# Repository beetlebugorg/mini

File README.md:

# Mini

<picture>
  <source media="(prefers-color-scheme: dark)" srcset="docs/lineart/img/hero-dark.png">
  
</picture>

A Bluetooth desk speaker that you print in three colors of PLA. Two Dayton Audio PC68-4
drivers and a ZK-502C Bluetooth amplifier sit in a sealed box of 166 × 108 × 94 mm. The
grille and the control strip snap on over four flush socket head screws.

- Website: https://beetlebug.org/mini/
- Spec sheet and build steps: [docs/Bluespeaker-Mini-Specs.pdf](docs/Bluespeaker-Mini-Specs.pdf)
- Drawings, 12 sheets: [docs/Bluespeaker-Mini-Drawings.pdf](docs/Bluespeaker-Mini-Drawings.pdf)
- Engineering report: [docs/Bluespeaker-Mini-Engineering-Report.pdf](docs/Bluespeaker-Mini-Engineering-Report.pdf)
- Design notes: [docs/MINI.md](docs/MINI.md)

## Build the files

1. `uv run cad/mini_report.py --step` writes the STEP parts.
2. `docs/lineart/build.sh` writes the line-art images and the spec sheet PDF.
3. `uv run cad/mini_drawings.py` writes the drawing sheets.
4. `uv run --with pymupdf cad/mini_report.py --pdf` writes the engineering report.

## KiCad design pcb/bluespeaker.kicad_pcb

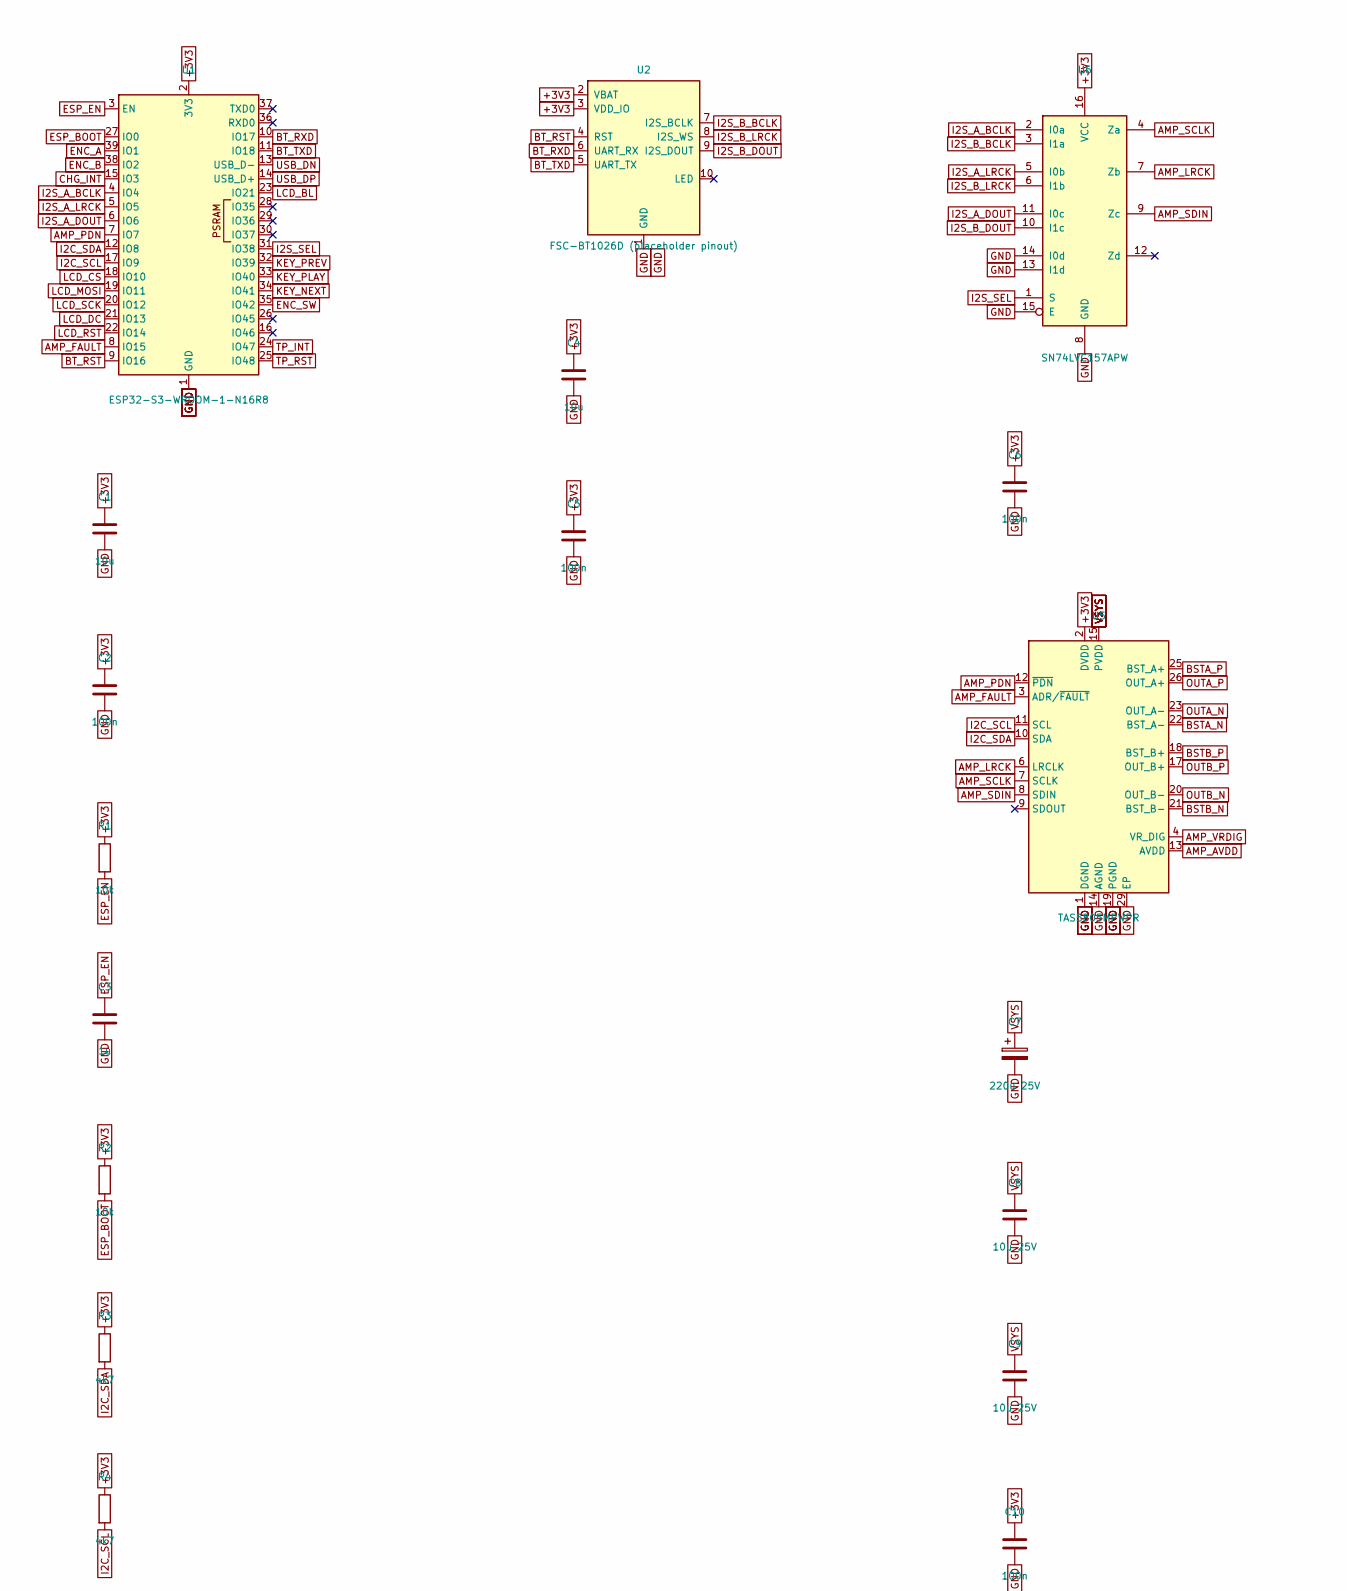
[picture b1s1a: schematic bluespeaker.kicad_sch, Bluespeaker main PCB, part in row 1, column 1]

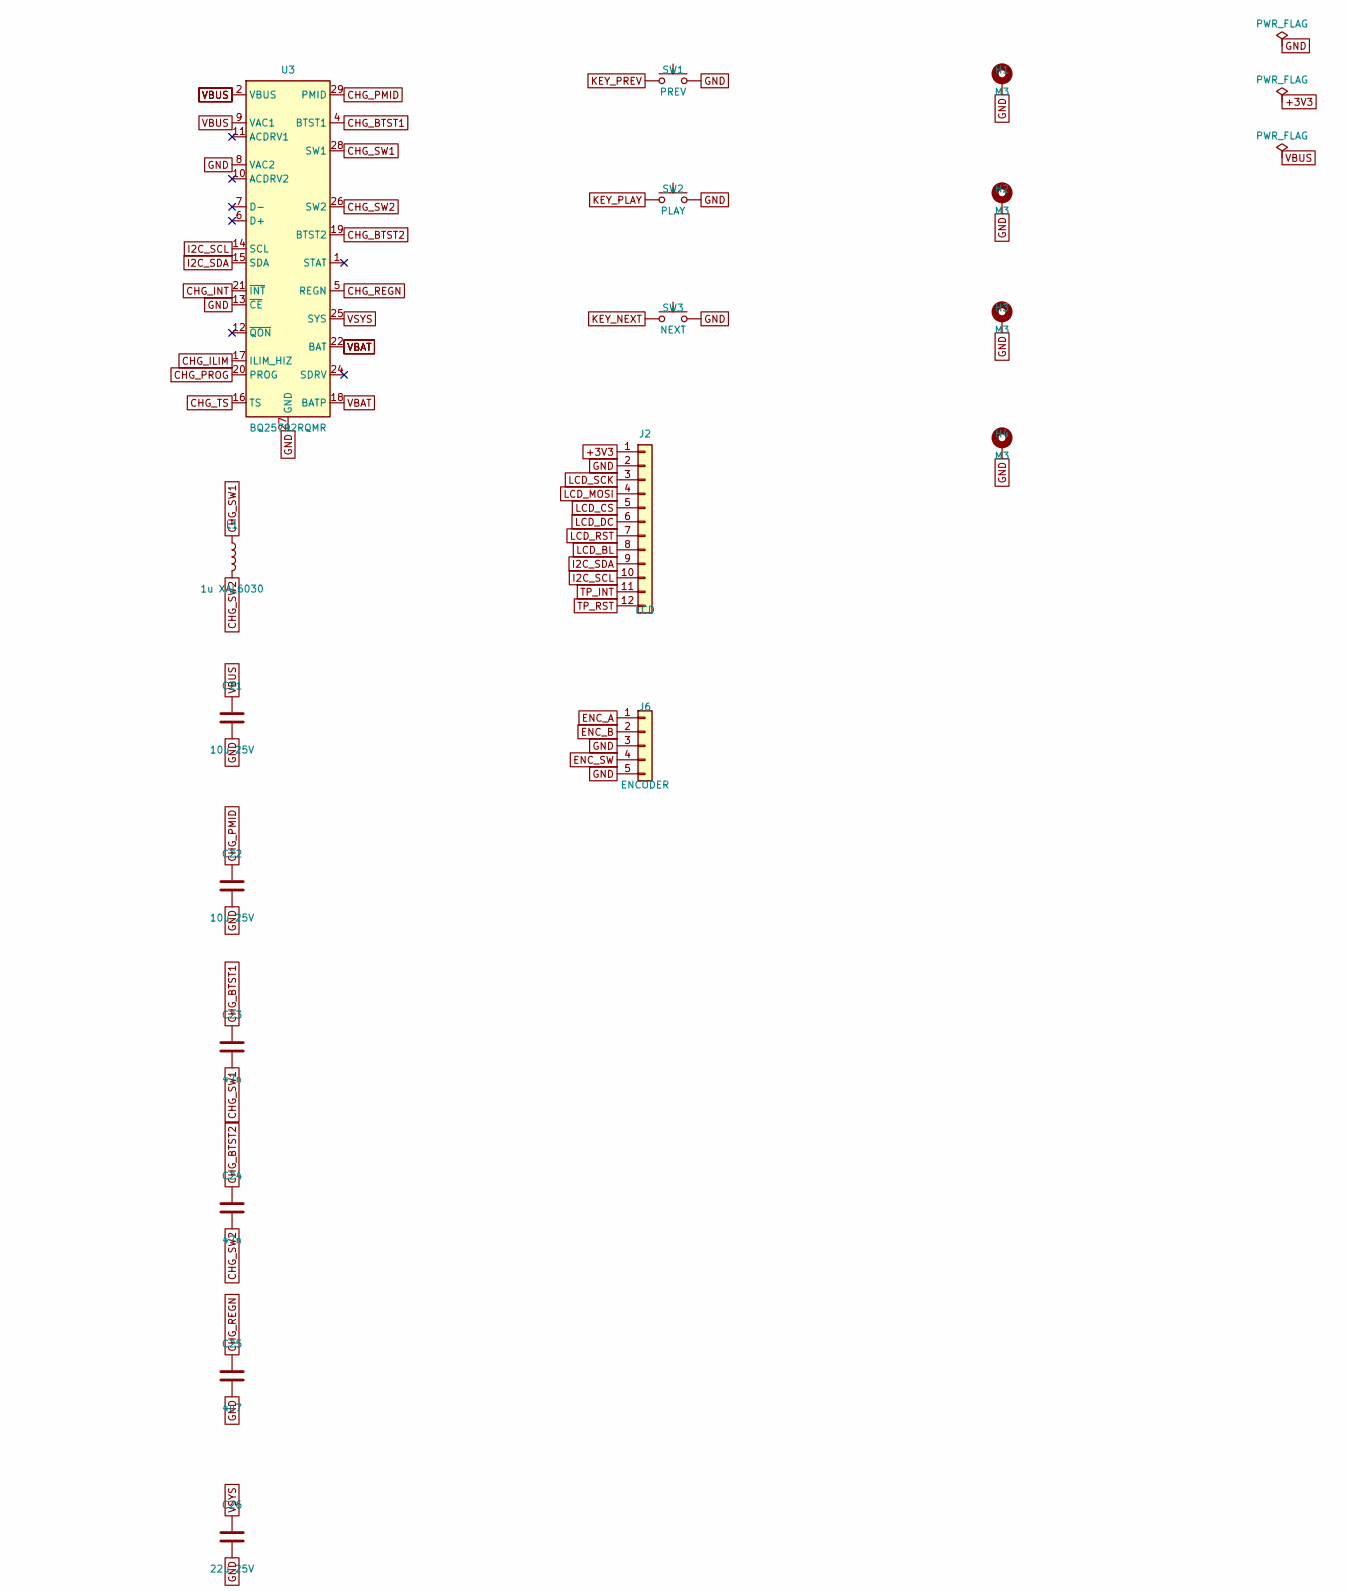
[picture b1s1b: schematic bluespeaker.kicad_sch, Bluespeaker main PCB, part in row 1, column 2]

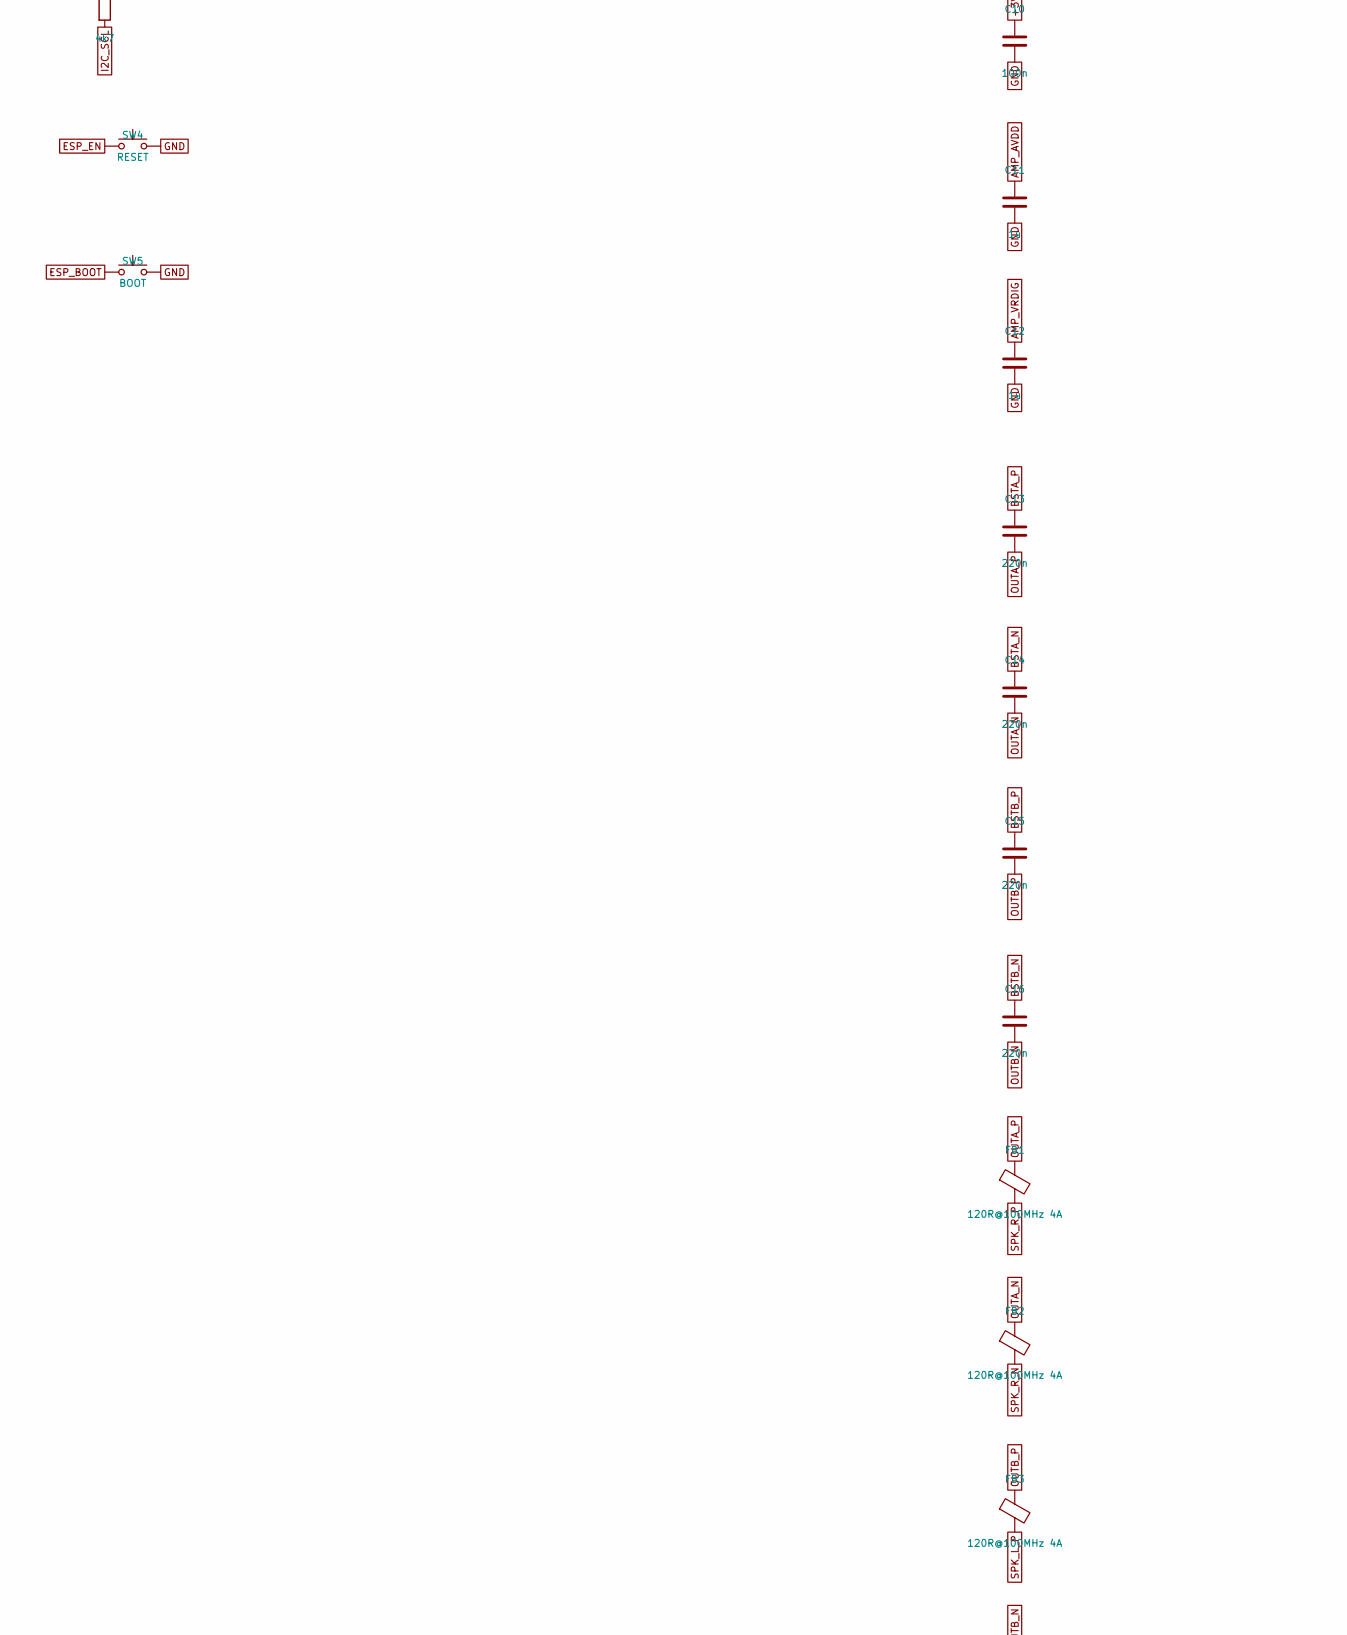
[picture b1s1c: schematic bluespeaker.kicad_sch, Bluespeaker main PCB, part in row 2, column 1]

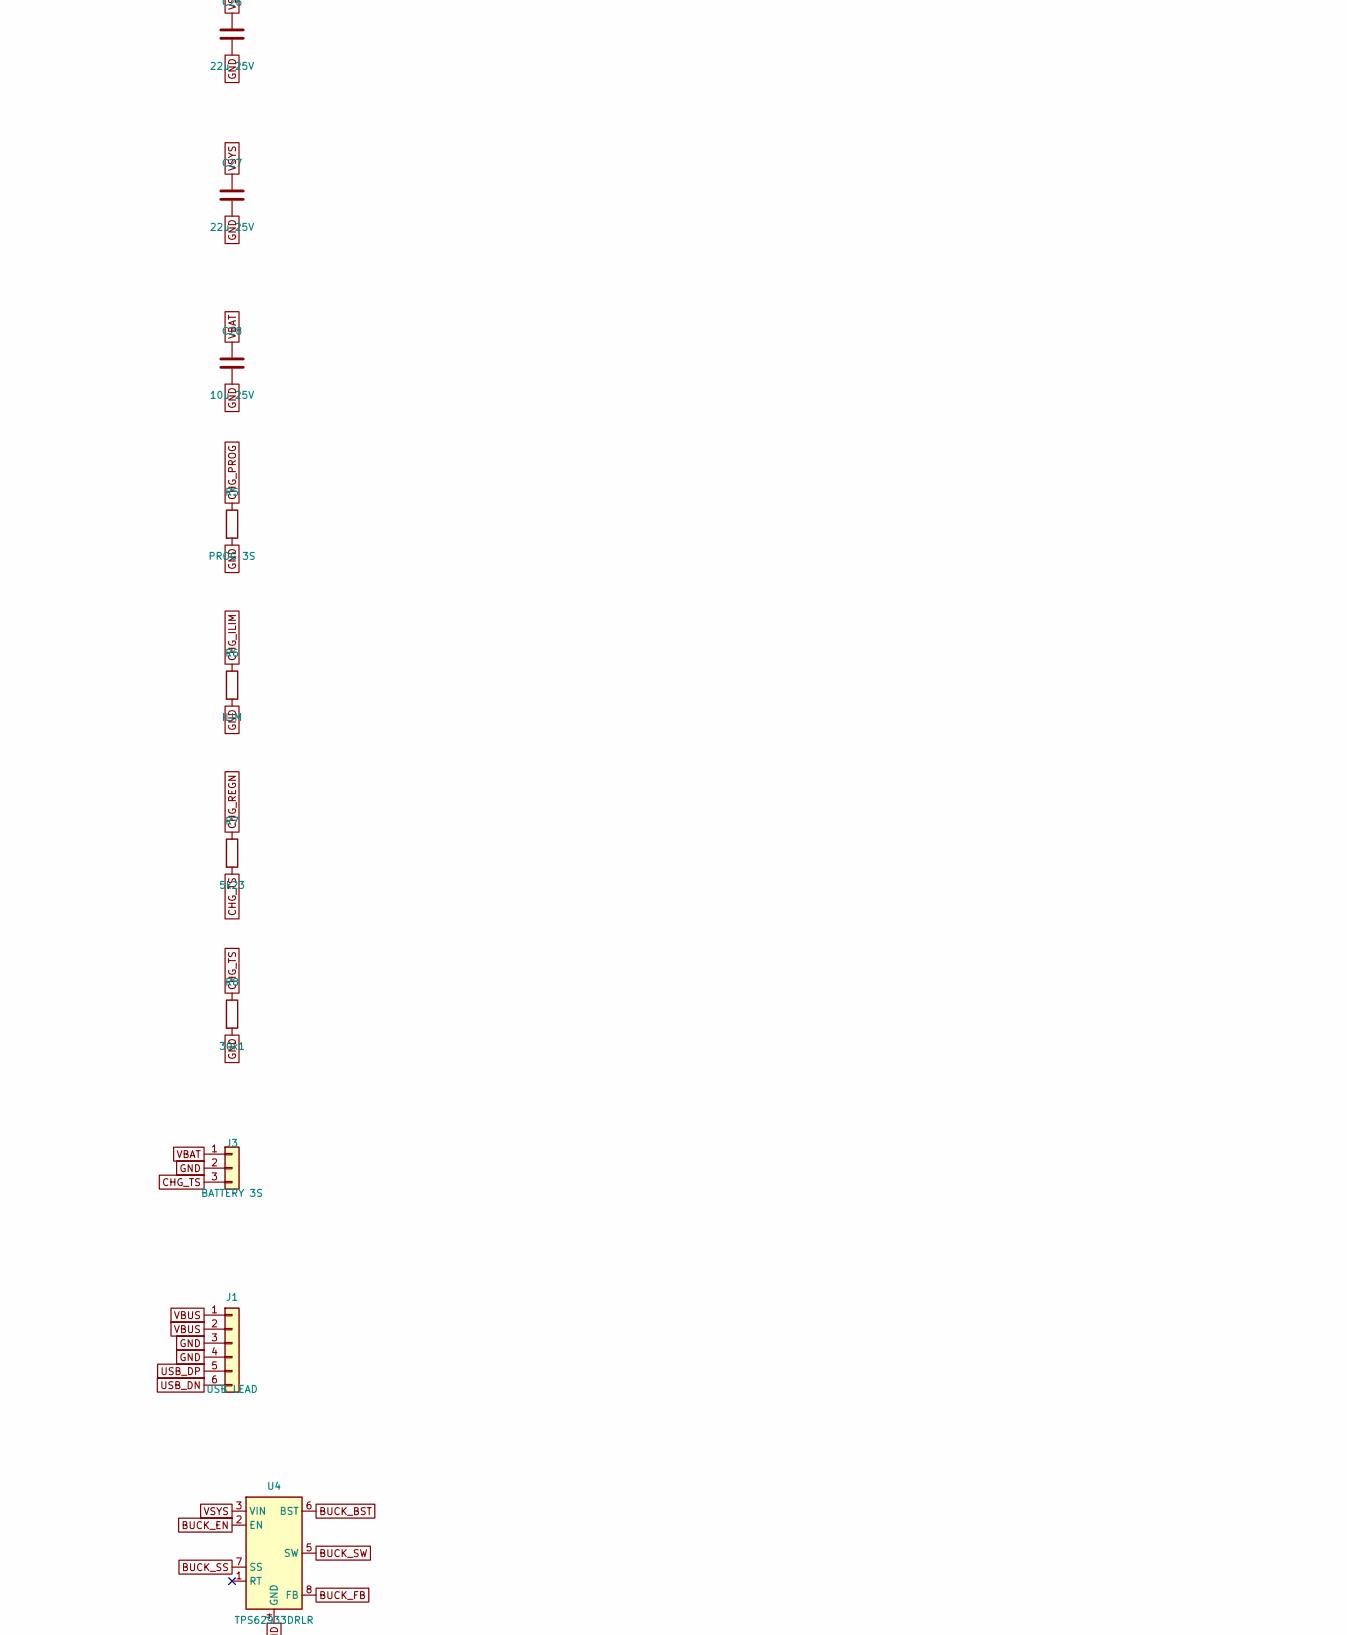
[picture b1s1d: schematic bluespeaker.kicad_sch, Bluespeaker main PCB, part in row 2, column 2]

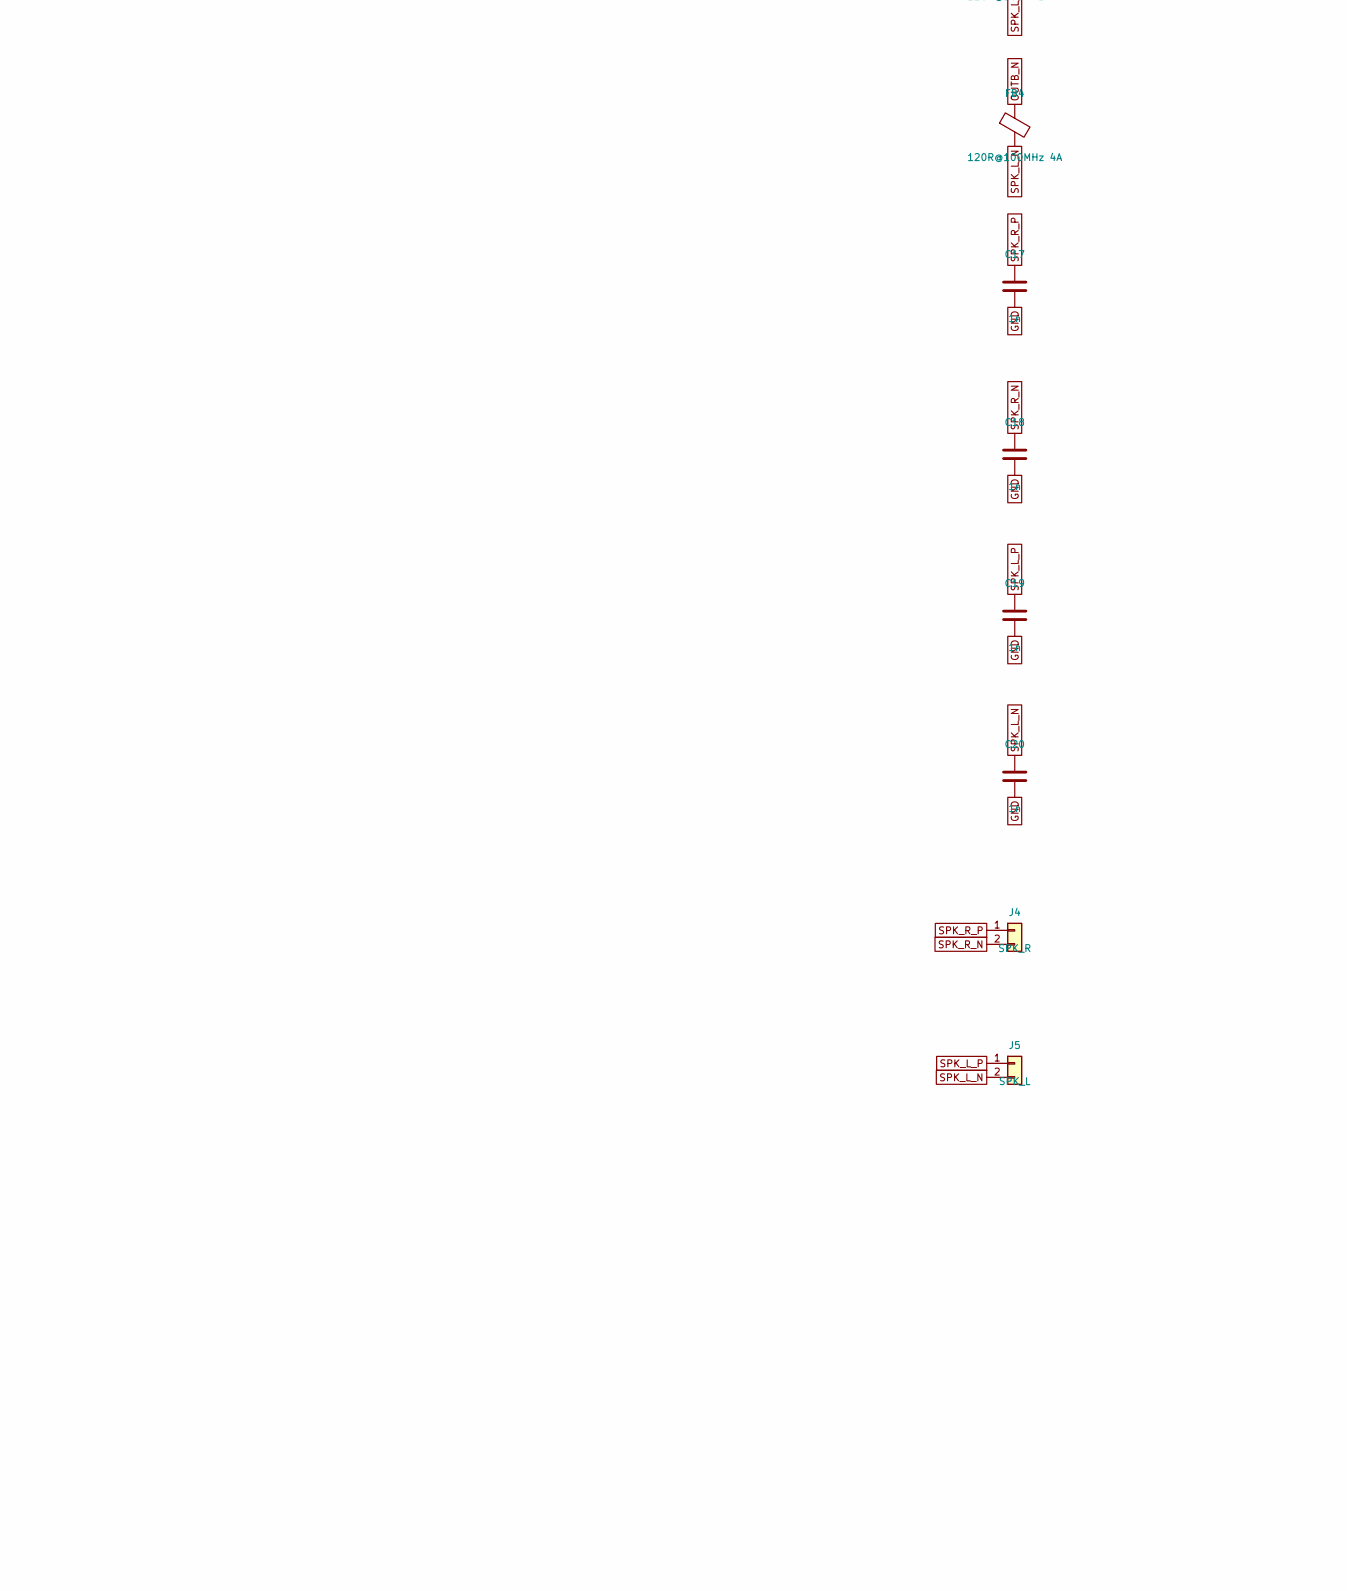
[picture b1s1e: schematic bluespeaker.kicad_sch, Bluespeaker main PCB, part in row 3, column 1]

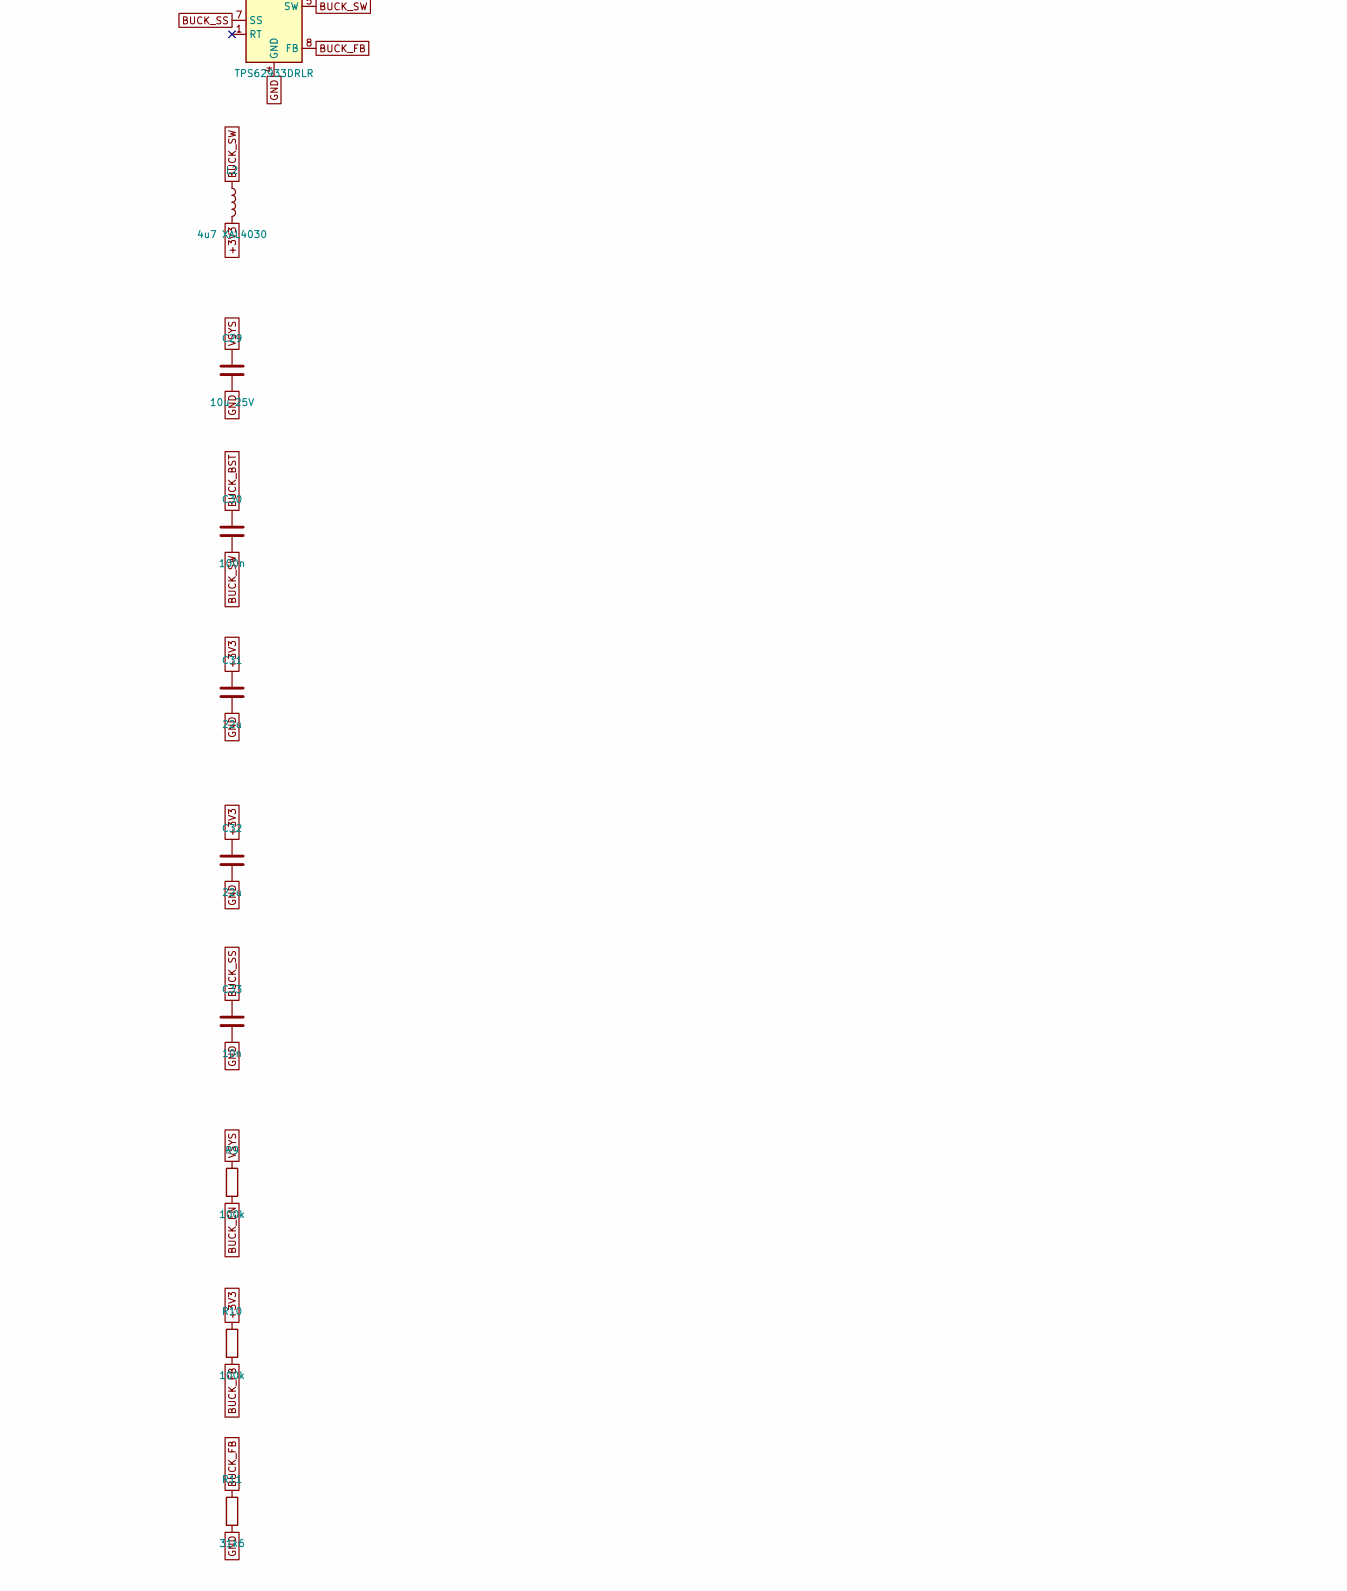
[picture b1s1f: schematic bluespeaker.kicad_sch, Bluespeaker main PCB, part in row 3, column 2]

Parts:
C1, C4: 10u; C_0805_2012Metric
C2, C5, C6, C10, C30: 100n; C_0603_1608Metric
C3, C11, C12: 1u; C_0603_1608Metric
C7: 220u 25V; CP_Elec_6.3x7.7
C8, C9, C21, C22, C28, C29: 10u 25V; C_1206_3216Metric
C13, C14, C15, C16: 220n; C_0603_1608Metric
C17, C18, C19, C20: 1n; C_0603_1608Metric
C23, C24: 47n; C_0603_1608Metric
C25: 4u7; C_0603_1608Metric
C26, C27: 22u 25V; C_1206_3216Metric
C31, C32: 22u; C_0805_2012Metric
C33: 10n; C_0603_1608Metric
FB1, FB2, FB3, FB4: 120R@100MHz 4A; L_1206_3216Metric
H1, H2, H3, H4: M3; MountingHole_3.2mm_M3_Pad
J1: USB LEAD; JST_PH_B6B-PH-K_1x06_P2.00mm_Vertical
J2: LCD; Hirose_FH12-12S-0.5SH_1x12-1MP_P0.50mm_Horizontal
J3: BATTERY 3S; JST_XH_B3B-XH-A_1x03_P2.50mm_Vertical
J4: SPK_R; JST_PH_B2B-PH-K_1x02_P2.00mm_Vertical
J5: SPK_L; JST_PH_B2B-PH-K_1x02_P2.00mm_Vertical
J6: ENCODER; JST_PH_B5B-PH-K_1x05_P2.00mm_Vertical
L1: 1u XAL6030; L_Coilcraft_XAL6030-XXX
L2: 4u7 XAL4030; L_Coilcraft_XAL4030-XXX
R1, R2: 10k; R_0603_1608Metric
R3, R4: 4k7; R_0603_1608Metric
R5: PROG 3S; R_0603_1608Metric
R6: ILIM; R_0603_1608Metric
R7: 5k23; R_0603_1608Metric
R8: 30k1; R_0603_1608Metric
R9, R10: 100k; R_0603_1608Metric
R11: 31k6; R_0603_1608Metric
SW1: PREV; SW_PUSH_6mm_H5mm
SW2: PLAY; SW_PUSH_6mm_H5mm
SW3: NEXT; SW_PUSH_6mm_H5mm
SW4: RESET; SW_SPST_TL3342
SW5: BOOT; SW_SPST_TL3342
U1: ESP32-S3-WROOM-1-N16R8; ESP32-S3-WROOM-1
U2: FSC-BT1026D (placeholder pinout); Feasycom_FSC-BT1026D
U3: BQ25792RQMR; Texas_RQM0029A_VQFN-29_4x4mm_P0.4mm
U4: TPS62933DRLR; SOT-583-8
U5: TAS5805MPWPR; TSSOP-28-1EP_4.4x9.7mm_P0.65mm_EP3.4x9.7mm_Mask3.1x4.05mm_T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
U6: SN74LVC157APW; TSSOP-16_4.4x5mm_P0.65mm

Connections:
+3V3: C1.1, C2.1, C4.1, C5.1, C6.1, C10.1, C31.1, C32.1, J2.1, L2.2, R1.1, R2.1, R3.1, R4.1, R10.1, U1.2 (3V3), U2.2 (VBAT), U2.3 (VDD_IO), U5.2 (DVDD), U6.16 (VCC)
AMP_AVDD: C11.1, U5.13 (AVDD)
AMP_FAULT: U1.8 (IO15), U5.3 (ADR/~FAULT)
AMP_LRCK: U5.6 (LRCLK), U6.7 (Zb)
AMP_PDN: U1.7 (IO7), U5.12 (~PDN)
AMP_SCLK: U5.7 (SCLK), U6.4 (Za)
AMP_SDIN: U5.8 (SDIN), U6.9 (Zc)
AMP_VRDIG: C12.1, U5.4 (VR_DIG)
BSTA_N: C14.1, U5.22 (BST_A-)
BSTA_P: C13.1, U5.25 (BST_A+)
BSTB_N: C16.1, U5.21 (BST_B-)
BSTB_P: C15.1, U5.18 (BST_B+)
BT_RST: U1.9 (IO16), U2.4 (RST)
BT_RXD: U1.10 (IO17), U2.6 (UART_RX)
BT_TXD: U1.11 (IO18), U2.5 (UART_TX)
BUCK_BST: C30.1, U4.6 (BST)
BUCK_EN: R9.2, U4.2 (EN)
BUCK_FB: R10.2, R11.1, U4.8 (FB)
BUCK_SS: C33.1, U4.7 (SS)
BUCK_SW: C30.2, L2.1, U4.5 (SW)
CHG_BTST1: C23.1, U3.4 (BTST1)
CHG_BTST2: C24.1, U3.19 (BTST2)
CHG_ILIM: R6.1, U3.17 (ILIM_HIZ)
CHG_INT: U1.15 (IO3), U3.21 (~INT)
CHG_PMID: C22.1, U3.29 (PMID)
CHG_PROG: R5.1, U3.20 (PROG)
CHG_REGN: C25.1, R7.1, U3.5 (REGN)
CHG_SW1: C23.2, L1.1, U3.28 (SW1)
CHG_SW2: C24.2, L1.2, U3.26 (SW2)
CHG_TS: J3.3, R7.2, R8.1, U3.16 (TS)
ENC_A: J6.1, U1.39 (IO1)
ENC_B: J6.2, U1.38 (IO2)
ENC_SW: J6.4, U1.35 (IO42)
ESP_BOOT: R2.2, SW5.1, U1.27 (IO0)
ESP_EN: C3.1, R1.2, SW4.1, U1.3 (EN)
GND: C1.2, C2.2, C3.2, C4.2, C5.2, C6.2, C7.2, C8.2, C9.2, C10.2, C11.2, C12.2, C17.2, C18.2, C19.2, C20.2, C21.2, C22.2, C25.2, C26.2, C27.2, C28.2, C29.2, C31.2, C32.2, C33.2, H1.1, H2.1, H3.1, H4.1, J1.3, J1.4, J2.2, J3.2, J6.3, J6.5, R5.2, R6.2, R8.2, R11.2, SW1.2, SW2.2, SW3.2, SW4.2, SW5.2, U1.1 (GND), U1.40 (GND), U1.41 (GND), U2.1 (GND), U2.11 (GND), U3.8 (VAC2), U3.13 (~CE), U3.27 (GND), U4.4 (GND), U5.1 (DGND), U5.5 (DGND), U5.14 (AGND), U5.19 (PGND), U5.24 (PGND), U5.29 (EP), U6.8 (GND), U6.13 (I1d), U6.14 (I0d), U6.15 (E)
I2C_SCL: J2.10, R4.2, U1.17 (IO9), U3.14 (SCL), U5.11 (SCL)
I2C_SDA: J2.9, R3.2, U1.12 (IO8), U3.15 (SDA), U5.10 (SDA)
I2S_A_BCLK: U1.4 (IO4), U6.2 (I0a)
I2S_A_DOUT: U1.6 (IO6), U6.11 (I0c)
I2S_A_LRCK: U1.5 (IO5), U6.5 (I0b)
I2S_B_BCLK: U2.7 (I2S_BCLK), U6.3 (I1a)
I2S_B_DOUT: U2.9 (I2S_DOUT), U6.10 (I1c)
I2S_B_LRCK: U2.8 (I2S_WS), U6.6 (I1b)
I2S_SEL: U1.31 (IO38), U6.1 (S)
KEY_NEXT: SW3.1, U1.34 (IO41)
KEY_PLAY: SW2.1, U1.33 (IO40)
KEY_PREV: SW1.1, U1.32 (IO39)
LCD_BL: J2.8, U1.23 (IO21)
LCD_CS: J2.5, U1.18 (IO10)
LCD_DC: J2.6, U1.21 (IO13)
LCD_MOSI: J2.4, U1.19 (IO11)
LCD_RST: J2.7, U1.22 (IO14)
LCD_SCK: J2.3, U1.20 (IO12)
OUTA_N: C14.2, FB2.1, U5.23 (OUT_A-)
OUTA_P: C13.2, FB1.1, U5.26 (OUT_A+)
OUTB_N: C16.2, FB4.1, U5.20 (OUT_B-)
OUTB_P: C15.2, FB3.1, U5.17 (OUT_B+)
SPK_L_N: C20.1, FB4.2, J5.2
SPK_L_P: C19.1, FB3.2, J5.1
SPK_R_N: C18.1, FB2.2, J4.2
SPK_R_P: C17.1, FB1.2, J4.1
TP_INT: J2.11, U1.24 (IO47)
TP_RST: J2.12, U1.25 (IO48)
USB_DN: J1.6, U1.13 (USB_D-)
USB_DP: J1.5, U1.14 (USB_D+)
VBAT: C28.1, J3.1, U3.18 (BATP), U3.22 (BAT), U3.23 (BAT)
VBUS: C21.1, J1.1, J1.2, U3.2 (VBUS), U3.3 (VBUS), U3.9 (VAC1)
VSYS: C7.1, C8.1, C9.1, C26.1, C27.1, C29.1, R9.1, U3.25 (SYS), U4.3 (VIN), U5.15 (PVDD), U5.16 (PVDD), U5.27 (PVDD), U5.28 (PVDD)

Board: 4 copper layers, 71 parts (4 on the bottom side), 69 nets, no tracks yet.
